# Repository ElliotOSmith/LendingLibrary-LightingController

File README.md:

# Lending Library Lighting Controller 

This simple controller based off of an ATTINY85 was designed to control lights within a lending library. It may be simple but it works. 

# Images

*Top of the board*
<br>

*Bottom of the board*
<br>

*Finished Installment*
<br>

<br>

<br>

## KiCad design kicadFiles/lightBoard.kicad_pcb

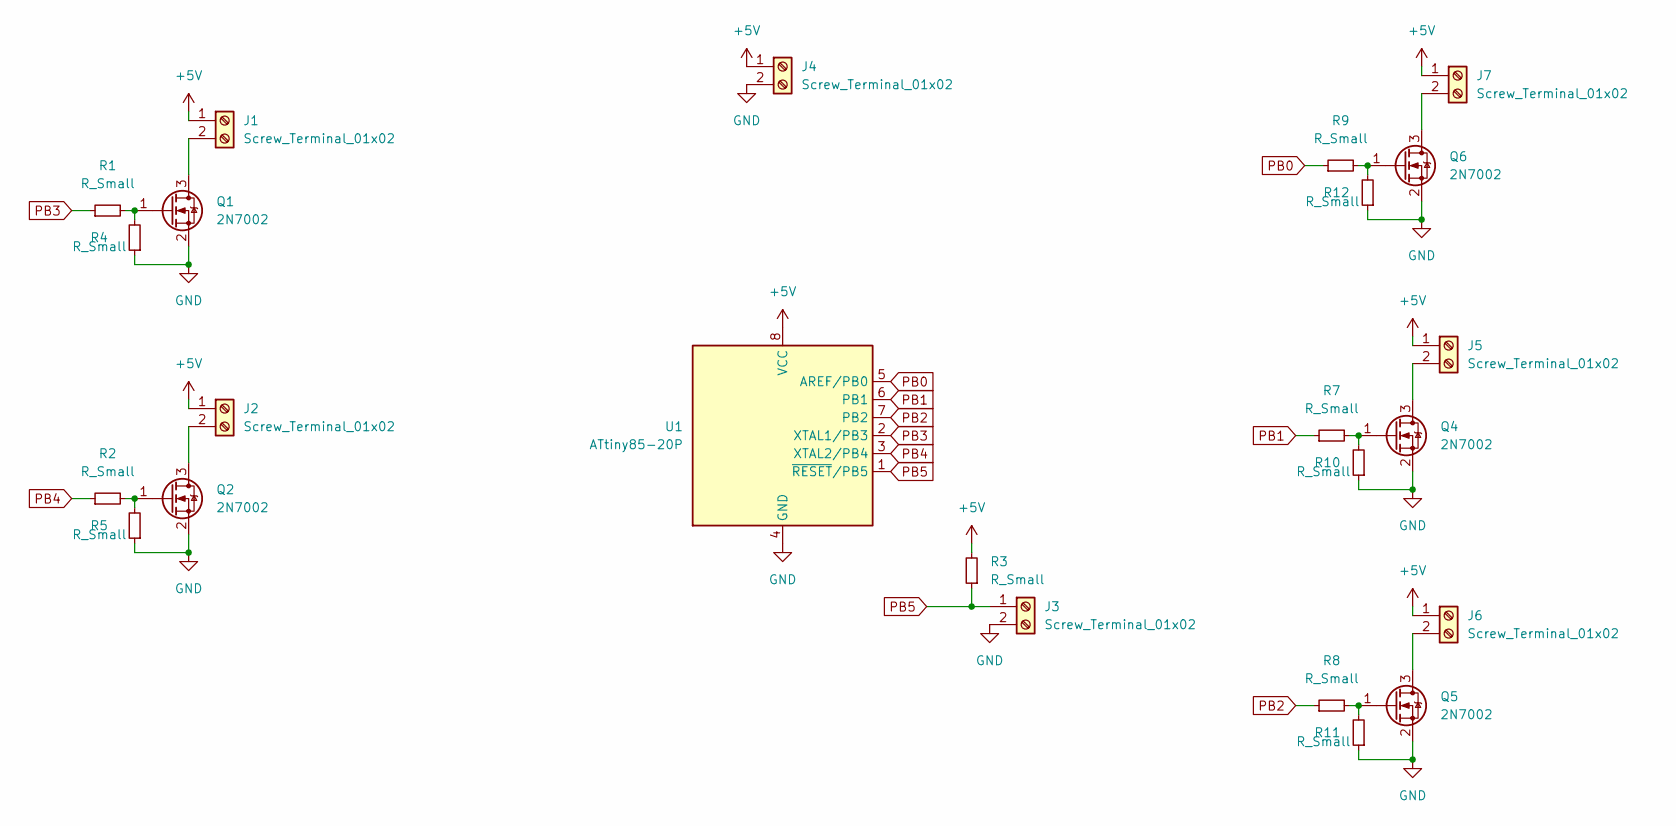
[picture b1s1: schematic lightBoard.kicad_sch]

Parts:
J1, J2, J3, J4, J5, J6, J7: Screw_Terminal_01x02; TerminalBlock_Altech_AK300-2_P5.00mm
Q1, Q2, Q4, Q5, Q6: 2N7002; SOT-23
R1, R2, R3, R4, R5, R7, R8, R9, R10, R11, R12: R_Small; R_0805_2012Metric
U1: ATtiny85-20P; DIP-8_W7.62mm

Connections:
+5V: J1.1, J2.1, J4.1, J5.1, J6.1, J7.1, R3.2, U1.8 (VCC)
GND: J3.2, J4.2, Q1.2 (S), Q2.2 (S), Q4.2 (S), Q5.2 (S), Q6.2 (S), R4.1, R5.1, R10.1, R11.1, R12.1, U1.4 (GND)
unnamed: J1.2, Q1.3 (D)
unnamed: J2.2, Q2.3 (D)
unnamed: J5.2, Q4.3 (D)
unnamed: J6.2, Q5.3 (D)
unnamed: J7.2, Q6.3 (D)
unnamed: Q1.1 (G), R1.2, R4.2
unnamed: Q2.1 (G), R2.2, R5.2
unnamed: Q4.1 (G), R7.2, R10.2
unnamed: Q5.1 (G), R8.2, R11.2
unnamed: Q6.1 (G), R9.2, R12.2
PB0: R9.1, U1.5 (AREF/PB0)
PB1: R7.1, U1.6 (PB1)
PB2: R8.1, U1.7 (PB2)
PB3: R1.1, U1.2 (XTAL1/PB3)
PB4: R2.1, U1.3 (XTAL2/PB4)
PB5: J3.1, R3.1, U1.1 (~RESET/PB5)

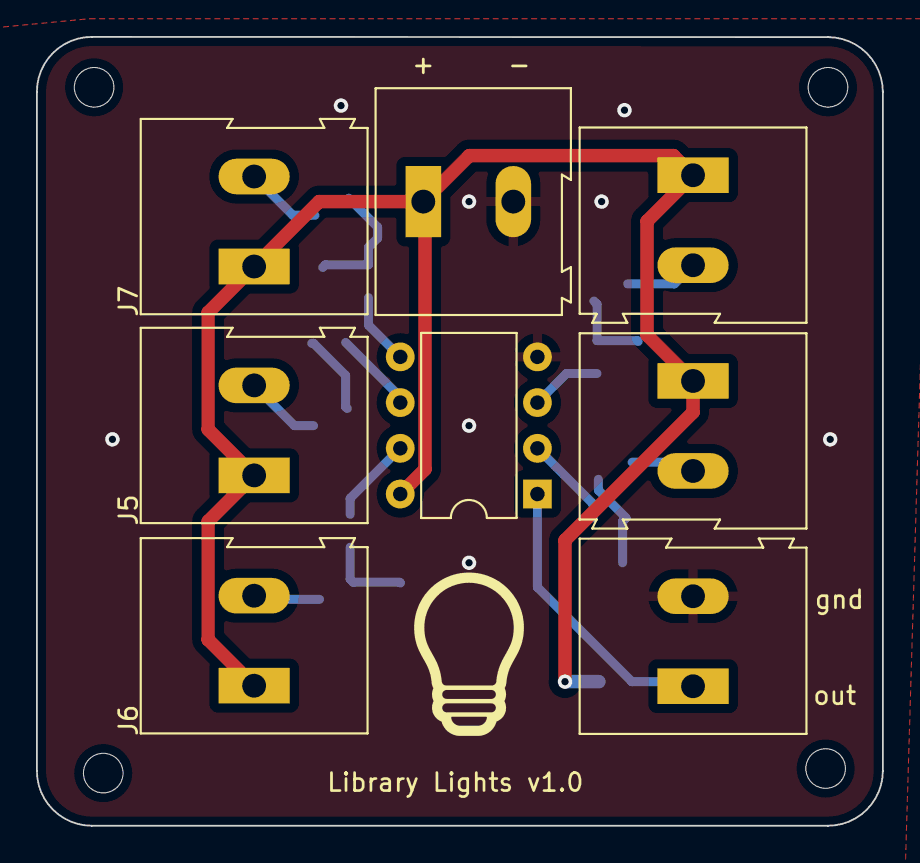
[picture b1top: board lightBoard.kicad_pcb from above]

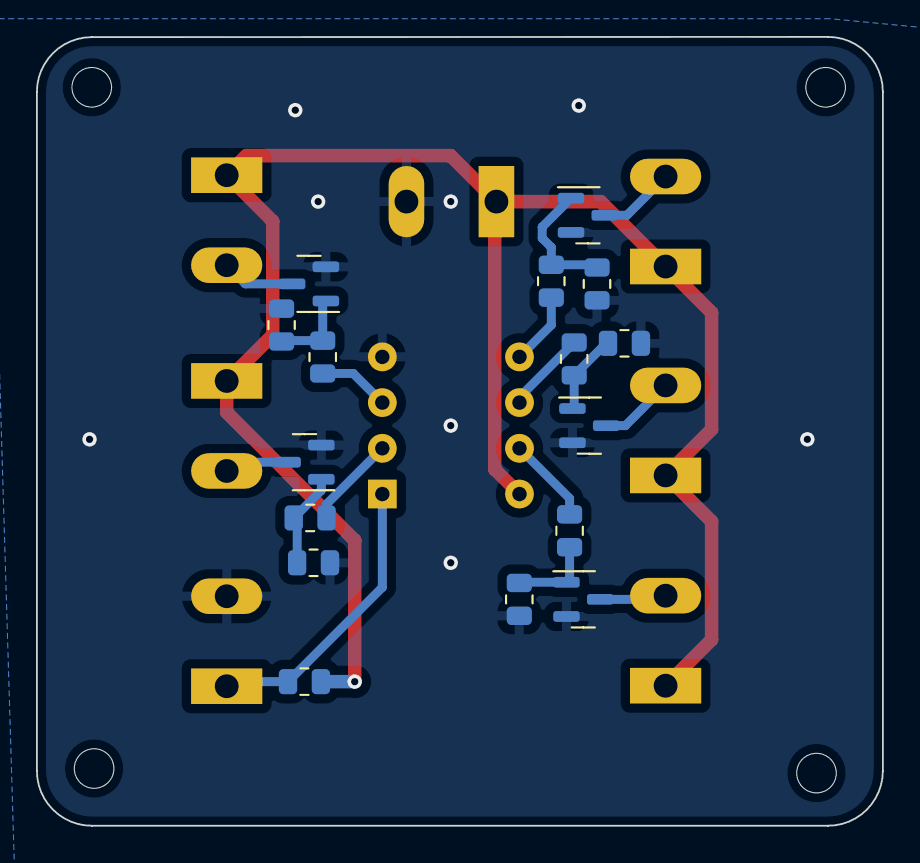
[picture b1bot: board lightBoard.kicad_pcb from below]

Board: 2 copper layers, 47.0 x 43.8 mm, 24 parts (16 on the bottom side), 18 nets.

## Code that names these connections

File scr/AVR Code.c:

#define F_CPU 1000000
#include <avr/io.h>
#include <util/delay.h>
#include <stdbool.h>

int main(void)
{
    
    DDRB &= ~(1 << PB5); //PB5 Input

    DDRB |= (1 << PB0);   //set PB0 as output
    DDRB |= (1 << PB1);   //set PB1 as output
    DDRB |= (1 << PB2);   //set PB2 as output
    DDRB |= (1 << PB3);   //set PB3 as output
    DDRB |= (1 << PB4);   //set PB4 as output

    bool doorClosed;
    bool countedDown = false;
    int timer = 0;

    while (1)
    {
        bool doorClosed = PINB & (1 << PB5);

        if(doorClosed){
            PORTB &= ~(1 << PB0); //turn off
            PORTB &= ~(1 << PB1);
            PORTB &= ~(1 << PB2);
            PORTB &= ~(1 << PB3);
            PORTB &= ~(1 << PB4);

            countedDown = false;
            timer = 0;
        }else{
            if(!countedDown){
                PORTB |= (1 << PB0); //turn on led
                PORTB |= (1 << PB1);
                PORTB |= (1 << PB2);
                PORTB |= (1 << PB3);
                PORTB |= (1 << PB4);
                
                while(!doorClosed){
                    _delay_ms(1000);
                    timer ++;
                    if(timer >= 120){
                        timer = 0;
                        countedDown = true;
                        PORTB &= ~(1 << PB0);// turn off
                        PORTB &= ~(1 << PB1);
                        PORTB &= ~(1 << PB2);
                        PORTB &= ~(1 << PB3);
                        PORTB &= ~(1 << PB4);
                        break;
                    }
                }
            }
        }
    }

}

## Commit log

2023-05-23 WORK YOU DUMB PEICE OF DUMBNESS
2023-05-23 asdf
2023-05-23 a;sdlfkja; ldsfk
2023-05-23 add files
2023-05-23 plz work
2023-05-23 add readme
2023-05-31 Added pdf
2023-05-31 added images
2023-05-31 removed stuffs
2023-05-31 readmmmes
2023-05-31 Readme Updates
2023-05-31 Readme Updates Final
2023-05-31 Added avr code
2023-05-31 File name change
2023-05-31 Code readme
2023-07-17 Added final installment and case
2023-07-17 case readme
